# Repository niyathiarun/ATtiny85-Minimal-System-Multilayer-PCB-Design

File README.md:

# ⭐ ATtiny85 Minimal System – Multilayer PCB Project

A compact multilayer PCB featuring the ATtiny85-20S microcontroller with proper power filtering, reset circuitry, and GPIO breakout.  
Designed as a learning-oriented embedded hardware project.

---

## 📌 **Objectives**

- Build a minimal, stable hardware setup for the ATtiny85 MCU  
- Learn multilayer PCB design flow  
- Implement proper decoupling and reset circuitry  
- Break out GPIO pins for programming & experimentation  
- Produce fabrication-ready Gerber & drill files  

---

## 🧩 **Project Overview**

This multilayer PCB includes everything required to run the ATtiny85 as a standalone microcontroller:

- ✔️ 5V Input  
- ✔️ Power filtering capacitors  
- ✔️ Reset switch + pull-up resistor  
- ✔️ GPIO/ISP header  
- ✔️ Stable multilayer routing  
- ✔️ Gerber + Drill + 3D View files included  

---

## 🔧 **Key Features**

- ATtiny85 in SOIC-8 package  
- Clean multilayer PCB layout  
- Professional schematic design  
- Proper decoupling (4.7µF + 0.1µF)  
- Reset control circuit  
- Compact and modular form factor  

---

## 🧠 **Working Principle**

### **1. Power Section**
- 5V input via header J1  
- C1 (4.7µF) → smooths low-frequency ripple  
- C2 (0.1µF) → handles fast switching noise  
- Ensures a clean and stable supply for the microcontroller

### **2. ATtiny85 Microcontroller (U1)**
- Operates on 5V  
- GPIO pins PB0–PB3 broken out via header J2  
- PB4 serves as Reset/I/O depending on configuration

### **3. Reset Circuit**
- R1 (10kΩ) keeps RESET pin pulled HIGH  
- SW1 pushes RESET LOW when pressed  
- Important for programming and debugging

### **4. GPIO / ISP Header**
Allows:
- ISP programming using USBasp / Arduino as ISP  
- Attaching sensors, LEDs, buttons, communication modules  
- General experimentation with ATtiny85 GPIOs  

---

## 🧰 **Applications**

This minimalist ATtiny85 board can be used for:

- Mini IoT nodes  
- Wearable electronics  
- LED drivers / light patterns  
- Sensor-based automation  
- Button-controlled gadgets  
- Low-power embedded systems  
- DIY hobby electronics  
- Educational microcontroller projects  

---

## 🧱 **Components Used**

| Component | Purpose |
|----------|---------|
| **ATtiny85-20S** | Main microcontroller |
| **C1 – 4.7µF** | Bulk decoupling |
| **C2 – 0.1µF** | High-frequency filtering |
| **R1 – 10kΩ** | Reset pull-up |
| **SW1** | Reset push button |
| **J1** | 5V power connector |
| **J2** | GPIO/ISP breakout header |

---
### 🛠 Tools Used
- KiCad 9.0 for schematic & PCB design   
- Gerber viewer for verification  

---

### 📚 Learnings
- Designing a minimal microcontroller hardware system  
- Power integrity: decoupling capacitors and filtering  
- Reset circuitry design (pull-up + switch)  
- Multilayer routing and stack-up basics  
- Creating fabrication files (Gerber + drill)  
- Schematic organization & PCB best practices
  
---

## 📁 **Repository Structure**

```
/Schematic  
    ATtiny85_Schematic.png

/PCB  
    Gerber_Files/  
    Drill_Files/  
    PCB_Layout.png  

/3D_View  
    PCB_3D_view.png  

README.md
```

---

## 🚀 **Future Enhancements**

- USB-C input  
- Onboard 5V/3.3V regulator  
- Power/status indicator LED  
- I²C expansion header  
- Bootloader support  

---

## ✍️ **Author**

**Niyathi Arun Kurthkoti**  
ECE Student | Aspiring Embedded & PCB Design Engineer
🔗 www.linkedin.com/in/niyathiarun
---

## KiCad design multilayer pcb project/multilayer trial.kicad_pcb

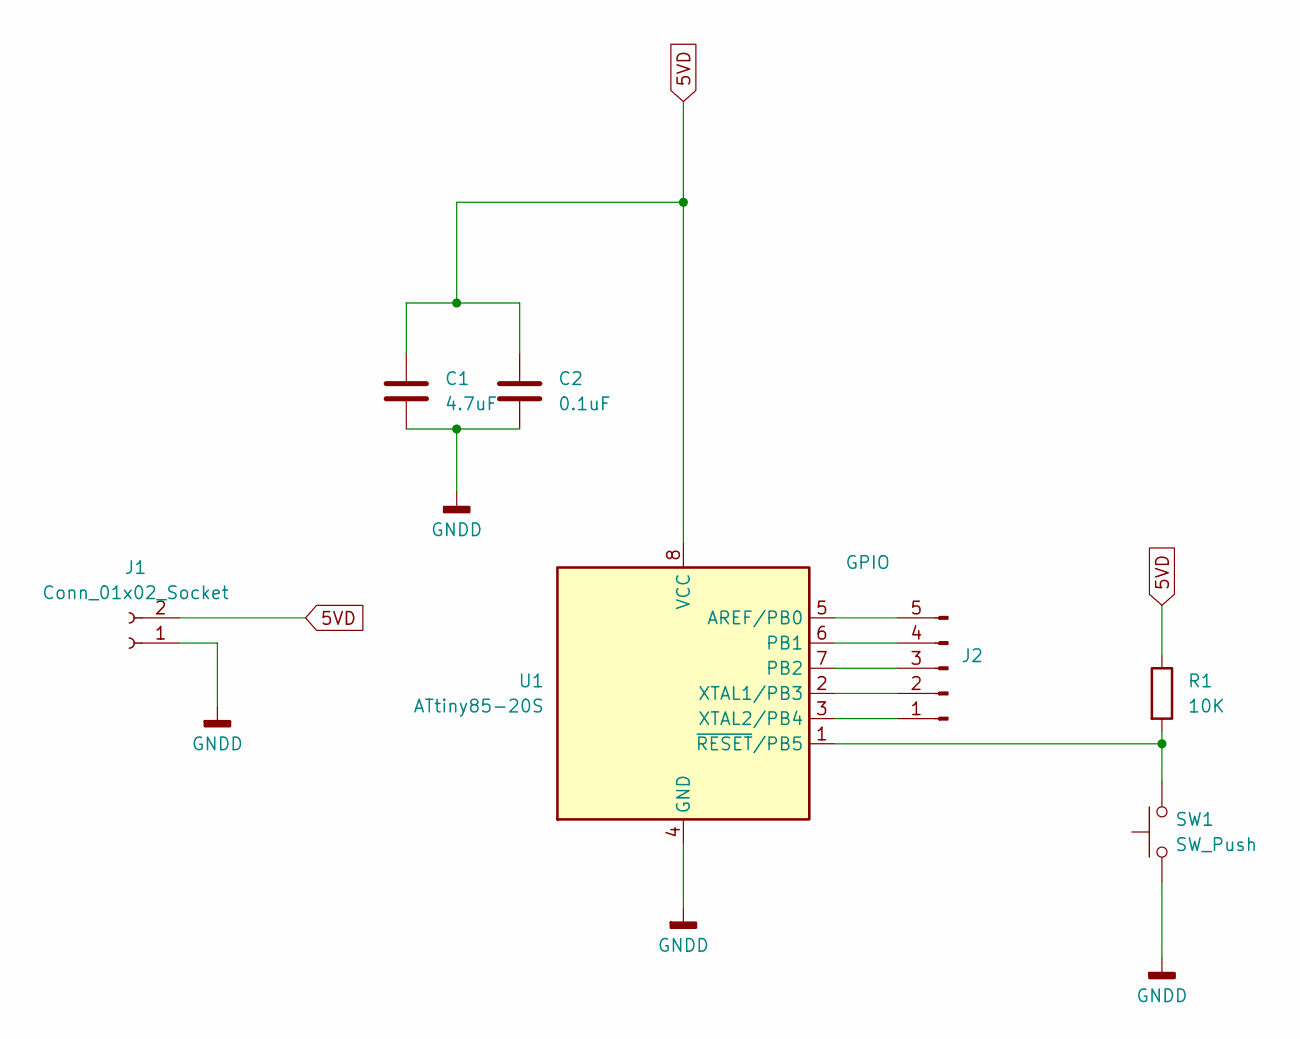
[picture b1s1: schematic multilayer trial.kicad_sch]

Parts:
C1: 4.7uF; C_0603_1608Metric
C2: 0.1uF; C_0603_1608Metric
J1: Conn_01x02_Socket; PinHeader_1x02_P2.54mm_Vertical
J2: GPIO; PinHeader_1x05_P2.54mm_Vertical
R1: 10K; R_0603_1608Metric
SW1: SW_Push; SW_PUSH_6mm
U1: ATtiny85-20S; SOIC-8_3.9x4.9mm_P1.27mm

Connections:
5VD: C1.1, C2.1, J1.2, R1.1, U1.8 (VCC)
GNDD: C1.2, C2.2, J1.1, SW1.1, U1.4 (GND)
unnamed: J2.1, U1.3 (XTAL2/PB4)
unnamed: J2.2, U1.2 (XTAL1/PB3)
unnamed: J2.3, U1.7 (PB2)
unnamed: J2.4, U1.6 (PB1)
unnamed: J2.5, U1.5 (AREF/PB0)
unnamed: R1.2, SW1.2, U1.1 (~RESET/PB5)

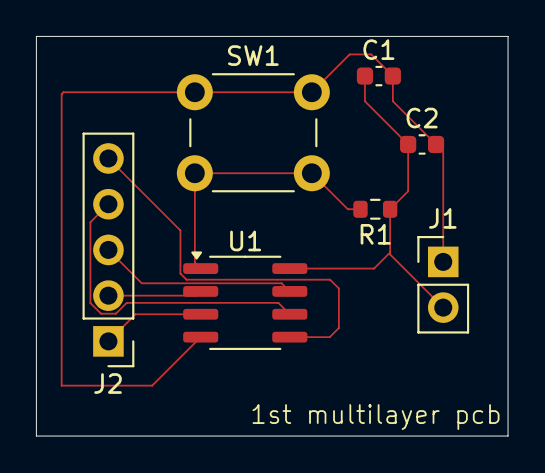
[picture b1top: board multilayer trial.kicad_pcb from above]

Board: 4 copper layers, 26.2 x 22.2 mm, 7 parts (0 on the bottom side), 8 nets.

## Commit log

2025-11-22 Revise README for ATtiny85 PCB project
    Updated README to enhance project description and structure.
2025-11-22 Enhance README with tools and learnings sections
    Added sections for tools used and learnings in README.
2025-11-22 update all files
    added Schematic, pcb layout and Gerber files
